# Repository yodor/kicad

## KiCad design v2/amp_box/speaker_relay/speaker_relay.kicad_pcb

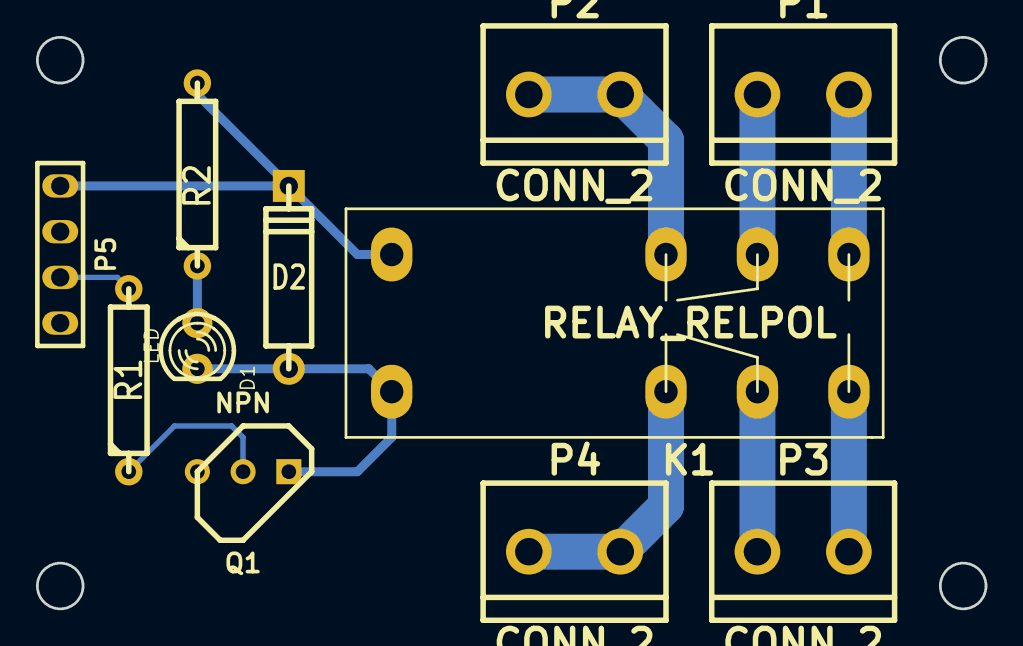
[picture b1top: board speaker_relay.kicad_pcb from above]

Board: 2 copper layers, 52.7 x 31.7 mm, 11 parts (0 on the bottom side), 12 nets.

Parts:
D1: LED; LED-3MM
D2: DIODE; D4
K1: RELAY_RELPOL; relay_V23042
P1, P2, P3, P4: CONN_2; bornier2
P5: CONN_4; PIN_ARRAY_4x1
Q1: NPN; TO92-123
R1: 4.1K; R4
R2: 680R; R4

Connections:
/5V: D2.2, K1.1, P5.1, R2.2
/AGND_L: K1.6, P2.1, P2.2
/AGND_R: K1.3, P4.1, P4.2
/EN: P5.3, R1.2
/OUT_L: K1.8, P1.2
/OUT_R: K1.5, P3.2
/SPK_L: K1.7, P1.1
/SPK_R: K1.4, P3.1
GND: P5.2, P5.4, Q1.1
unnamed: D1.1, R2.1
unnamed: Q1.2, R1.1
unnamed: D1.2, D2.1, K1.2, Q1.3

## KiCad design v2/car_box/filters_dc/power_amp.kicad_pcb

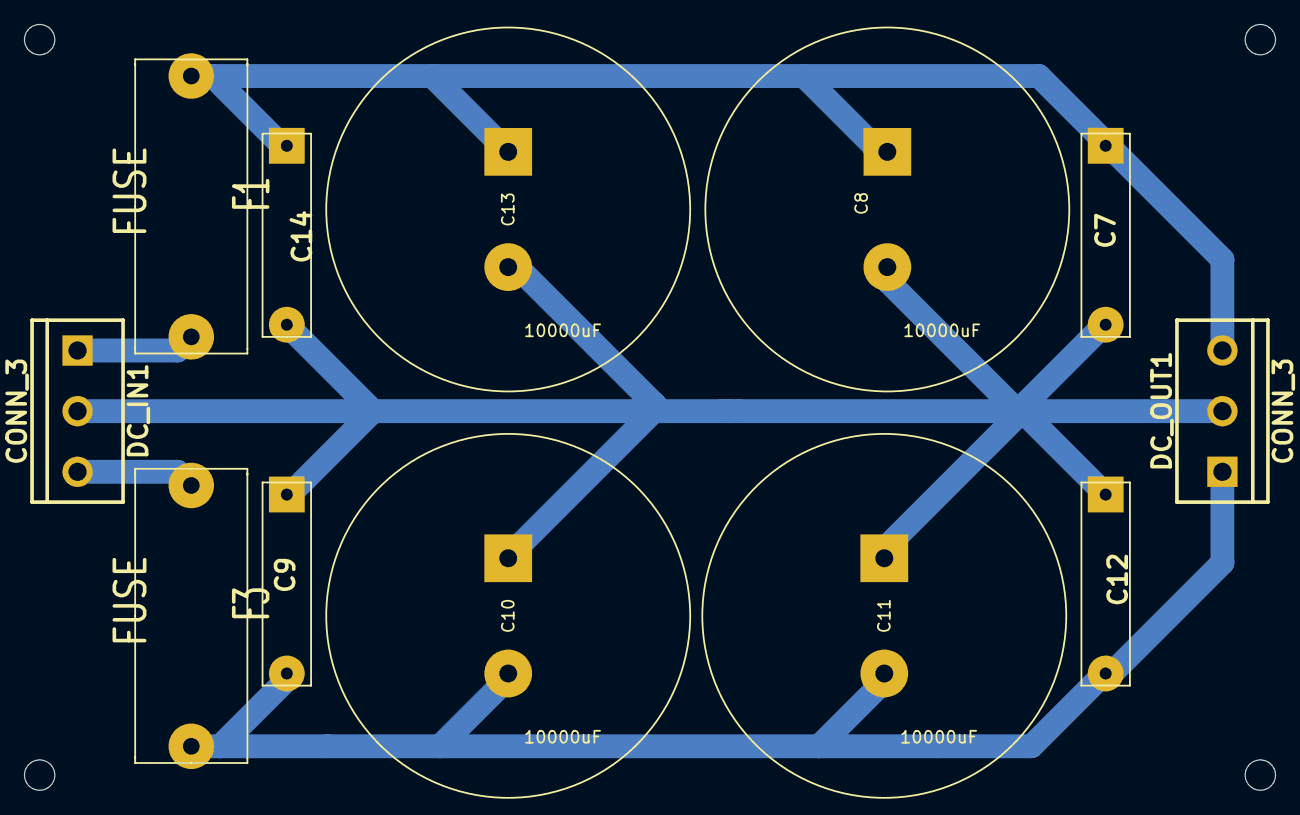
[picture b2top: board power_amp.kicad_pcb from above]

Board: 2 copper layers, 104.8 x 64.1 mm, 12 parts (0 on the bottom side), 5 nets.

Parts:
C7, C9, C12, C14: 100nF; CP6
C8, C10, C11, C13: 10000uF; capacitor_big
DC_IN1: CONN_3; bornier3
DC_OUT1: CONN_3; bornier3
F1, F3: FUSE; FUSE5-20

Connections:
unnamed: C9.2, C10.2, C11.2, C12.2, DC_OUT1.1, F3.1
unnamed: DC_IN1.1, F1.1
unnamed: DC_IN1.3, F3.2
unnamed: C7.1, C8.1, C13.1, C14.1, DC_OUT1.3, F1.2
unnamed: C7.2, C8.2, C9.1, C10.1, C11.1, C12.1, C13.2, C14.2, DC_IN1.2, DC_OUT1.2

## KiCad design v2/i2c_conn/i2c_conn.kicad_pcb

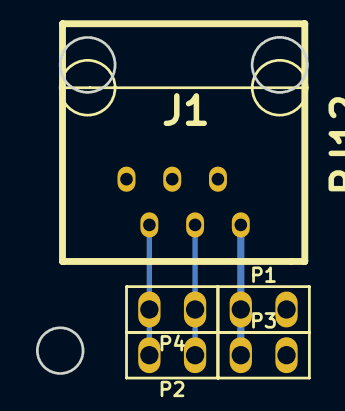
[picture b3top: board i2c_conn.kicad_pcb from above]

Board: 2 copper layers, 15.0 x 18.7 mm, 5 parts (0 on the bottom side), 4 nets.

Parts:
J1: RJ12; RJ12_MOD6
P1, P2, P3, P4: CONN_2; PIN_ARRAY_2X1

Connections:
/5V: J1.1, P1.1, P3.1
/SCL: J1.5, P2.2, P4.2
/SDA: J1.3, P2.1, P4.1
GND: J1.2, J1.4, J1.6, P1.2, P3.2

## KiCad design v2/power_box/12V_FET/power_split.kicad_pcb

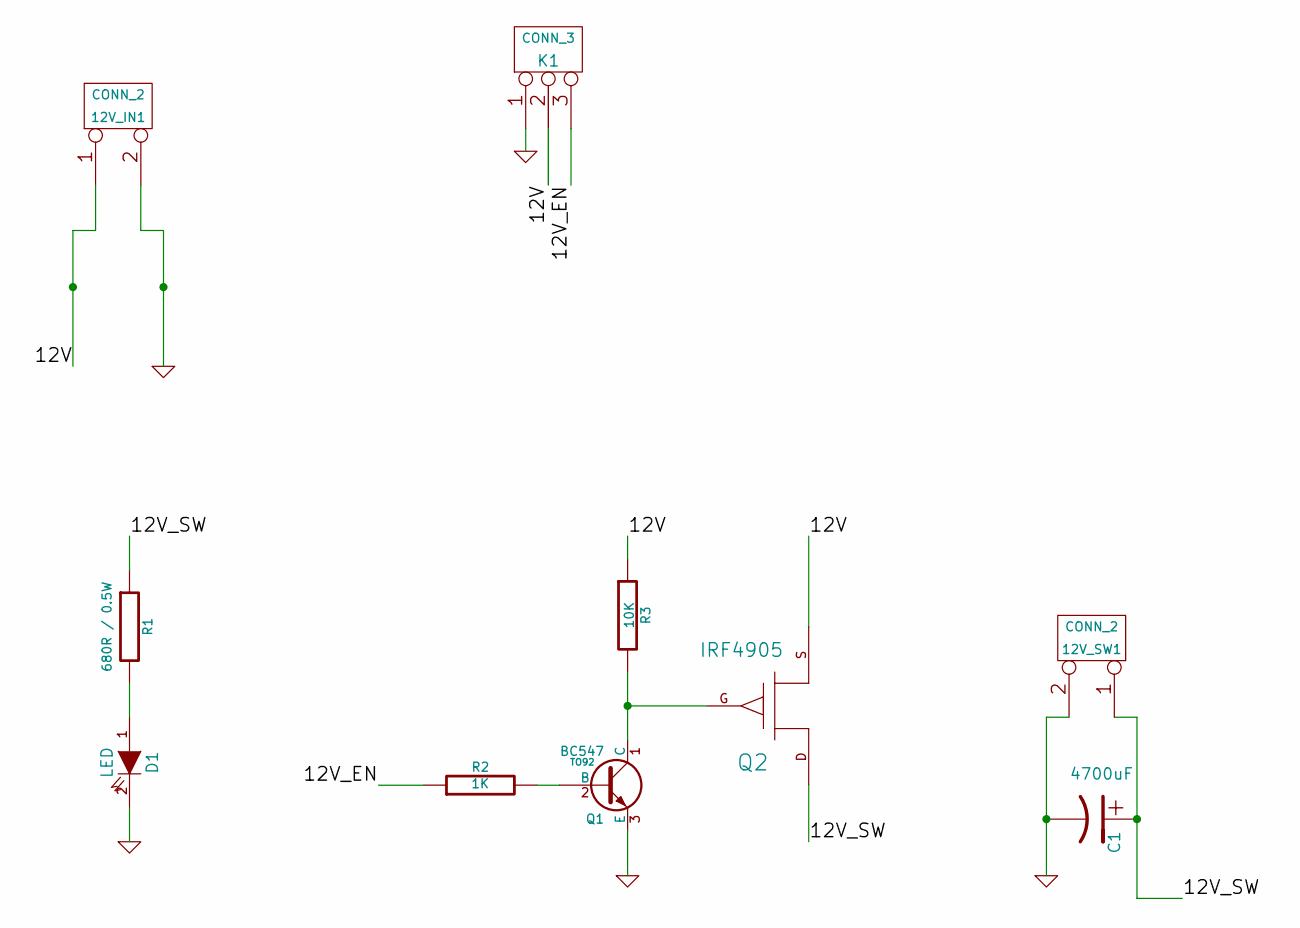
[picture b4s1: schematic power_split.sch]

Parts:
12V_IN1, 12V_SW1: CONN_2
C1: 4700uF
D1: LED
K1: CONN_3
Q1: BC547; TO92
Q2: IRF4905
R1: 680R / 0.5W
R2: 1K
R3: 10K

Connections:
/12V: 12V_IN1.1, K1.2 (PM), Q2.S, R3.1
/12V_EN: K1.3, R2.1
/12V_SW: 12V_SW1.1, C1.1, Q2.D, R1.1
GND: 12V_IN1.2 (PM), 12V_SW1.2 (PM), C1.2, D1.2 (K), K1.1, Q1.3 (E)
unnamed: Q1.2 (B), R2.2
unnamed: D1.1 (A), R1.2
unnamed: Q1.1 (C), Q2.G, R3.2

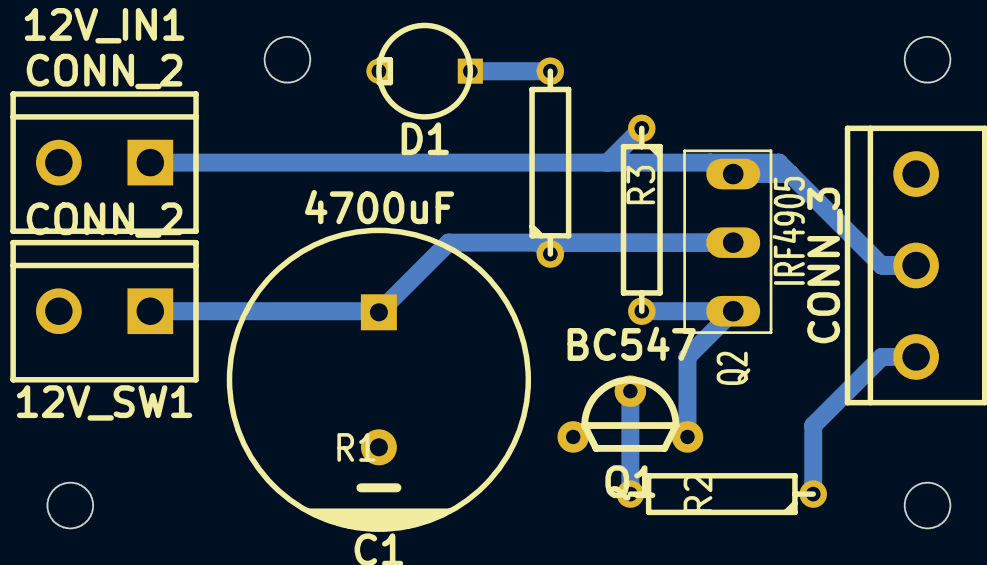
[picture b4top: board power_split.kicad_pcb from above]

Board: 2 copper layers, 50.2 x 27.3 mm, 10 parts (0 on the bottom side), 7 nets.

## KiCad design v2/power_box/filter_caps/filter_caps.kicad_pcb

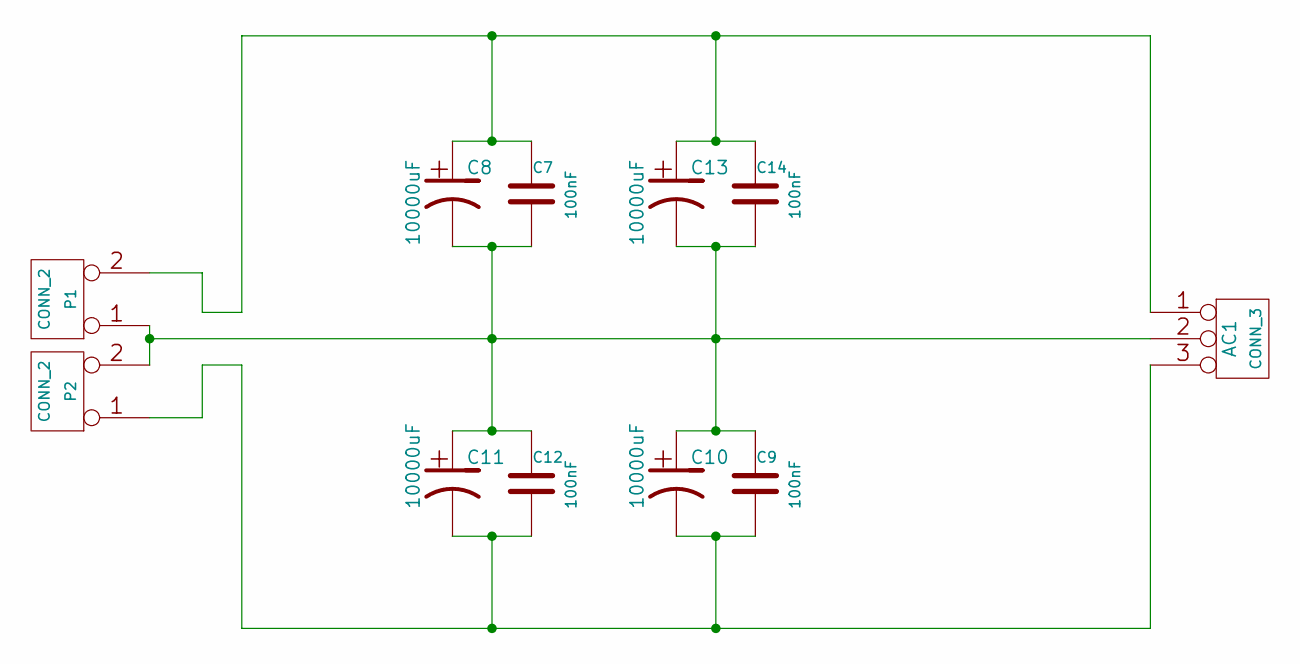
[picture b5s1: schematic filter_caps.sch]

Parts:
AC1: CONN_3
C7, C9, C12, C14: 100nF
C8, C10, C11, C13: 10000uF
P1, P2: CONN_2

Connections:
unnamed: AC1.1, C7.1, C8.1, C13.1, C14.1, P1.2 (PM)
unnamed: AC1.3, C9.2, C10.2, C11.2, C12.2, P2.1
unnamed: AC1.2 (PM), C7.2, C8.2, C9.1, C10.1, C11.1, C12.1, C13.2, C14.2, P1.1, P2.2 (PM)

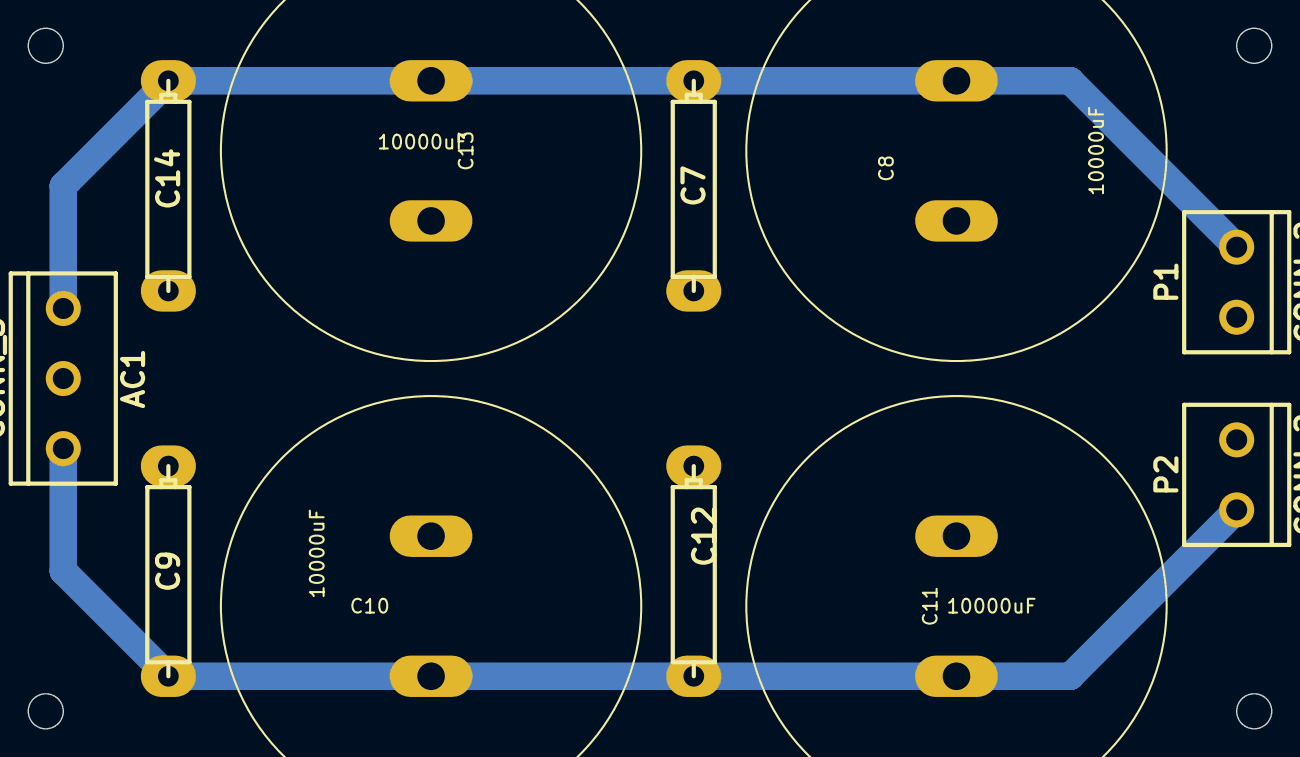
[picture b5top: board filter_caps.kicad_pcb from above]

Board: 2 copper layers, 90.2 x 50.8 mm, 11 parts (0 on the bottom side), 3 nets.

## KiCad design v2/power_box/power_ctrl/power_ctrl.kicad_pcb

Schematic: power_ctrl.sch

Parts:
5V_AUX1, 12V_AUX1, 12V_IN1, 12V_SW1: CONN_2; bornier2
AUXA1: CONN_2; Pin_Header_Straight_1x02
AUXD1, AUXD2: CONN_2; Pin_Header_Straight_1x02
C1, C3, C4, C6, C7: 100nF; C_Rect_L7_W2_P5
C2: 470uF; C_Radial_D5_L6_P2.5
C5, C8: 10uF; C_Radial_D5_L6_P2.5
C9: 4.7uF; C_Radial_D5_L11_P2.5
C10: 4700uF; C_Radial_D10_L21_P5
D1, D2: DIODE; Diode_DO-35_SOD27_Horizontal_RM10
D3, D4: LED; LED-3MM
FB1, FB2, FB3, FB4, FB5: FILTER; R4
J1: Atmega328; DIP-28_W7.62mm_LongPads
J2: RJ12; RJ12_E
Q1: BC547; TO-92_Inline_Narrow_Oval
Q2: Q_PMOS_GDS; TO-220_Neutral123_Vertical_LargePads
R1, R4: 680R; R4
R2: 100R; R4
R3, R7: 1K; R4
R5: 10K; R4
R6: 680R / 0.5W; R4
U1: 7805; TO-220_Neutral123_Vertical_LargePads
i2c1: CONN_01X04; Pin_Header_Straight_1x04
ir1: CONN_4; Pin_Header_Straight_1x04
pwr_btn_led1: CONN_4; Pin_Header_Straight_1x04
soft_start1: CONN_4; Pin_Header_Straight_1x04

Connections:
/5V: 5V_AUX1.1, C7.2, C8.1, FB1.1, FB4.2, FB5.2, J1.1, R1.1, R2.2, i2c1.3, soft_start1.1
/12V: 12V_AUX1.1, 12V_IN1.1, D1.1 (A), Q2.3 (S), R5.1
/12V_EN: J1.5, R3.1
/12V_SW: 12V_SW1.1, C10.1, Q2.2 (D), R6.1
/AUXA1: AUXA1.1, J1.24
/AUXA2: AUXA1.2 (PM), J1.25
/AUXD1: AUXD1.1, J1.13
/AUXD2: AUXD1.2 (PM), J1.14
/AUXD3: AUXD2.1, J1.15
/AUXD4: AUXD2.2 (PM), J1.16
/EN_R1: J1.18, soft_start1.3
/EN_R2: J1.17, soft_start1.4
/IR_IN: J1.19, ir1.1
/PWR_BTN: J1.12, pwr_btn_led1.2
/PWR_LED: J1.11, R4.1
/SCL: FB2.2, J2.2, i2c1.1
/SDA: FB3.1, J2.5, i2c1.4
GND: 5V_AUX1.2 (PM), 12V_AUX1.2 (PM), 12V_IN1.2 (PM), 12V_SW1.2 (PM), C1.1, C2.2, C3.1, C4.1, C5.2, C6.2, C7.1, C8.2, C9.2, C10.2, D3.1, D4.1, J1.8, J1.22, J2.1, J2.3, J2.4, J2.6, Q1.3 (E), R7.2, U1.GND, i2c1.2, ir1.4, pwr_btn_led1.1, pwr_btn_led1.4, soft_start1.2
unnamed: C1.2, FB1.2, J1.7
unnamed: C2.1, C3.2, D1.2 (K), D2.2 (K), U1.VI
unnamed: C4.2, C5.1, D2.1 (A), FB4.1, U1.VO
unnamed: C6.1, FB5.1, J1.20, J1.21
unnamed: C9.1, R2.1, ir1.3
unnamed: D3.2, R1.2
unnamed: D4.2, R6.2
unnamed: FB2.1, J1.28
unnamed: FB3.2, J1.27
unnamed: Q1.1 (C), Q2.1 (G), R5.2
unnamed: Q1.2 (B), R3.2, R7.1
unnamed: R4.2, pwr_btn_led1.3

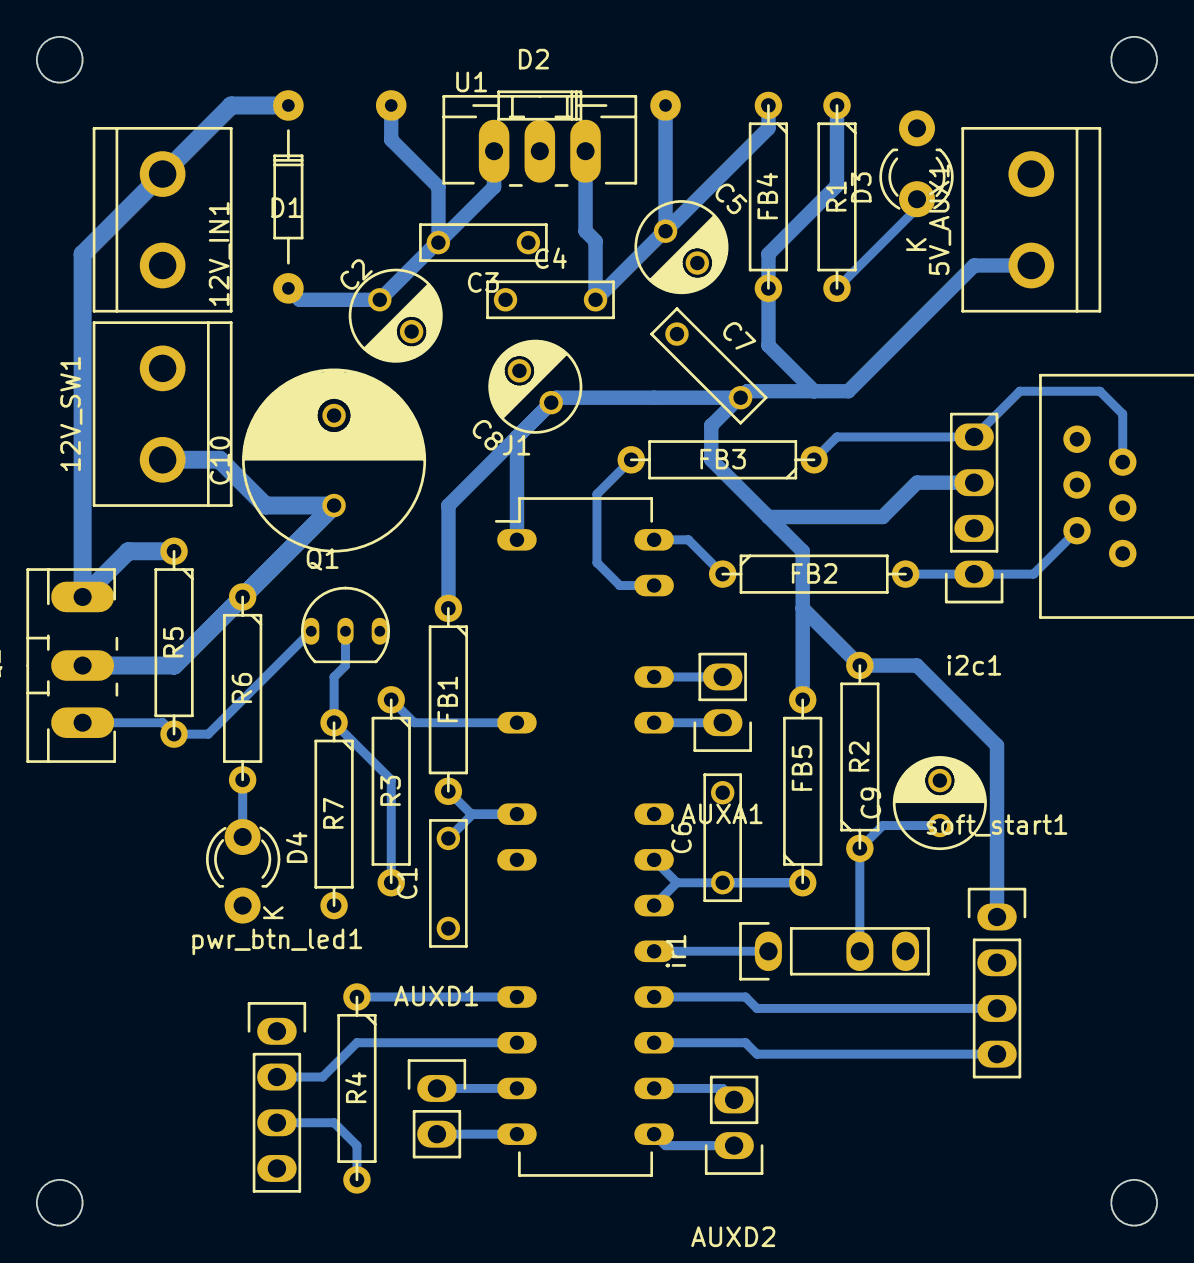
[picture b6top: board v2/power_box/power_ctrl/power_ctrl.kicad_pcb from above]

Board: 2 copper layers, 62.2 x 66.0 mm, 41 parts (0 on the bottom side), 30 nets.

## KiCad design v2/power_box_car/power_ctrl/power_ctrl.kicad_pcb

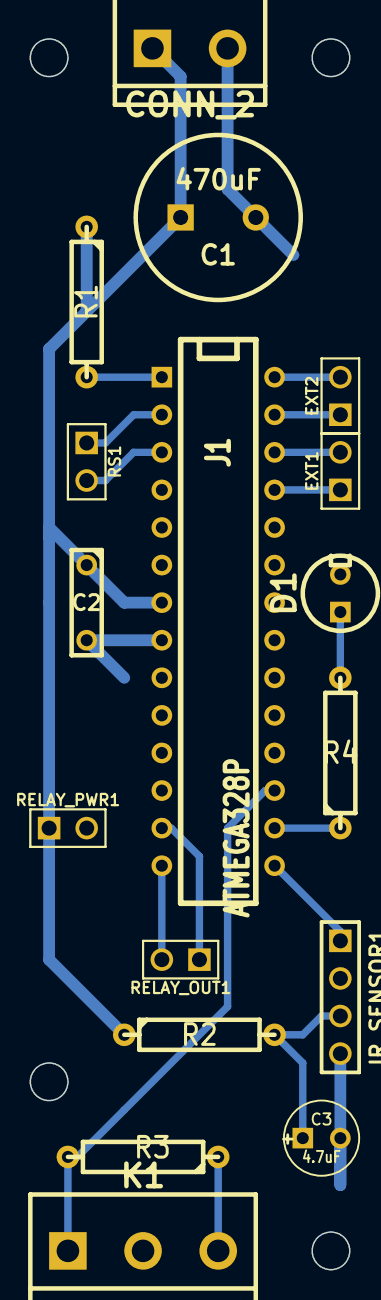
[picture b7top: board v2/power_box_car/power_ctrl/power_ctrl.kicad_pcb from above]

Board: 2 copper layers, 21.6 x 83.2 mm, 17 parts (0 on the bottom side), 17 nets.

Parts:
C1: 470uF; C2V10
C2: 100nF; C2
C3: 4.7uF; C1V5
D1: LED; LEDV
EXT1, EXT2: CONN_2; PIN_ARRAY_2X1
IR_SENSOR1: CONN_4; PIN_ARRAY_4x1
J1: ATMEGA328P; DIP-28__300
K1: CONN_3; bornier3
PWR_IN1: CONN_2; bornier2
R1: 4.7K; R4
R2: 100R; R4
R3: 10K; R4
R4: 680R; R4
RELAY_OUT1: CONN_2; PIN_ARRAY_2X1
RELAY_PWR1: CONN_2; PIN_ARRAY_2X1
RS1: CONN_2; PIN_ARRAY_2X1

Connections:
/5V: C1.1, C2.1, J1.7, PWR_IN1.1, R1.1, R2.1, RELAY_PWR1.1
/A0: EXT1.1, J1.25
/A1: EXT1.2, J1.26
/EN_R1: J1.13, RELAY_OUT1.1
/EN_R2: J1.14, RELAY_OUT1.2
/IR: IR_SENSOR1.1, J1.15
/LED_EN: J1.16, R4.1
/PWR_DIS: J1.17, K1.1, R3.2
/PWR_DIS_REMOTE: K1.3, R3.1
/SCL: EXT2.2, J1.28
/SDA: EXT2.1, J1.27
GND: C1.2, C2.2, C3.2, D1.2, IR_SENSOR1.4, J1.8, K1.2, PWR_IN1.2, RELAY_PWR1.2
unnamed: D1.1, R4.2
unnamed: J1.3, RS1.2
unnamed: J1.1, R1.2
unnamed: C3.1, IR_SENSOR1.3, R2.2
unnamed: J1.2, RS1.1

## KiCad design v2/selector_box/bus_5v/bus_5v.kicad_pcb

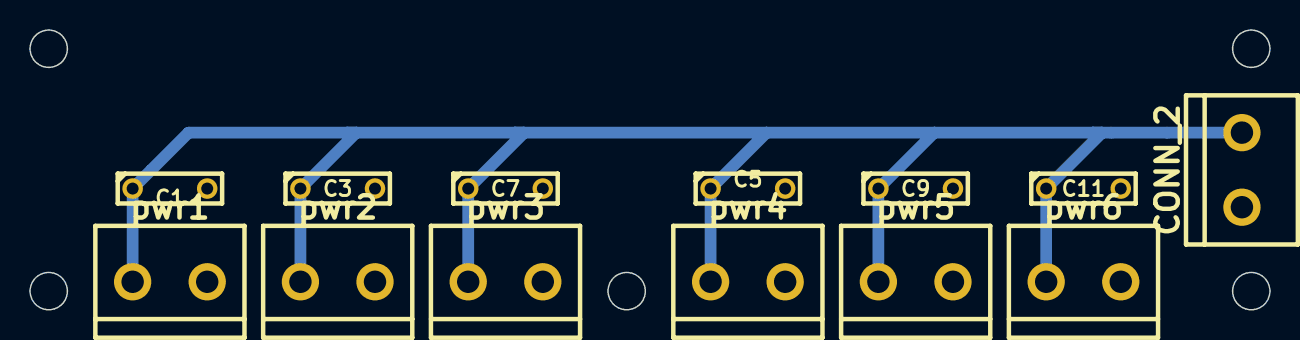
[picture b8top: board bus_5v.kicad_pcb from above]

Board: 2 copper layers, 84.5 x 19.1 mm, 13 parts (0 on the bottom side), 2 nets.

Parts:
C1, C3, C5, C7, C9, C11: 100nF; C2
P1: CONN_2; bornier2
pwr1, pwr2, pwr3, pwr4, pwr5, pwr6: CONN_2; bornier2

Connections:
/5V: C1.1, C3.1, C5.1, C7.1, C9.1, C11.1, P1.1, pwr1.1, pwr2.1, pwr3.1, pwr4.1, pwr5.1, pwr6.1
GND: C1.2, C3.2, C5.2, C7.2, C9.2, C11.2, P1.2, pwr1.2, pwr2.2, pwr3.2, pwr4.2, pwr5.2, pwr6.2
